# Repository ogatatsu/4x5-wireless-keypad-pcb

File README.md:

# 4x5-wireless-keypad-pcb

## 部品表

| Name | Qty | Description | Manufacturer
----|----|----|----
| U1 | 1 | BL652-SA-01 | LairdTech |
| Y1 | 1 | Crystal, FC-135, 32.768kHz, 9pF | EPSON |
| C1,C2 | 2 | Capacitor, 12pF, 1608 ||
| C3,C4 | 2 | Capacitor, 0.1uF, 1608 ||
| R1 | 1 | Resistor, 1k Ohm, 1608 ||
| R2 | 1 | Resistor, 330 Ohm, 1608 ||
| R3 | 1 | Resistor, 10k Ohm, 1608 ||
| D1~21 | 21 | Diode, 1N4148W | Diodes Incorporated |
| LED1 | 1 | Led, Red, 1608 ||
| LED2 | 1 | Led, Yellow Green, 1608 ||
| SW1~20 | 20 | Switch, Cherry Mx | Cherry |
| BT1,2 | 4 | Battery Clips, BC-0402 | COMFORTABLE ELECTRONIC |

## License

https://creativecommons.org/licenses/by/4.0/

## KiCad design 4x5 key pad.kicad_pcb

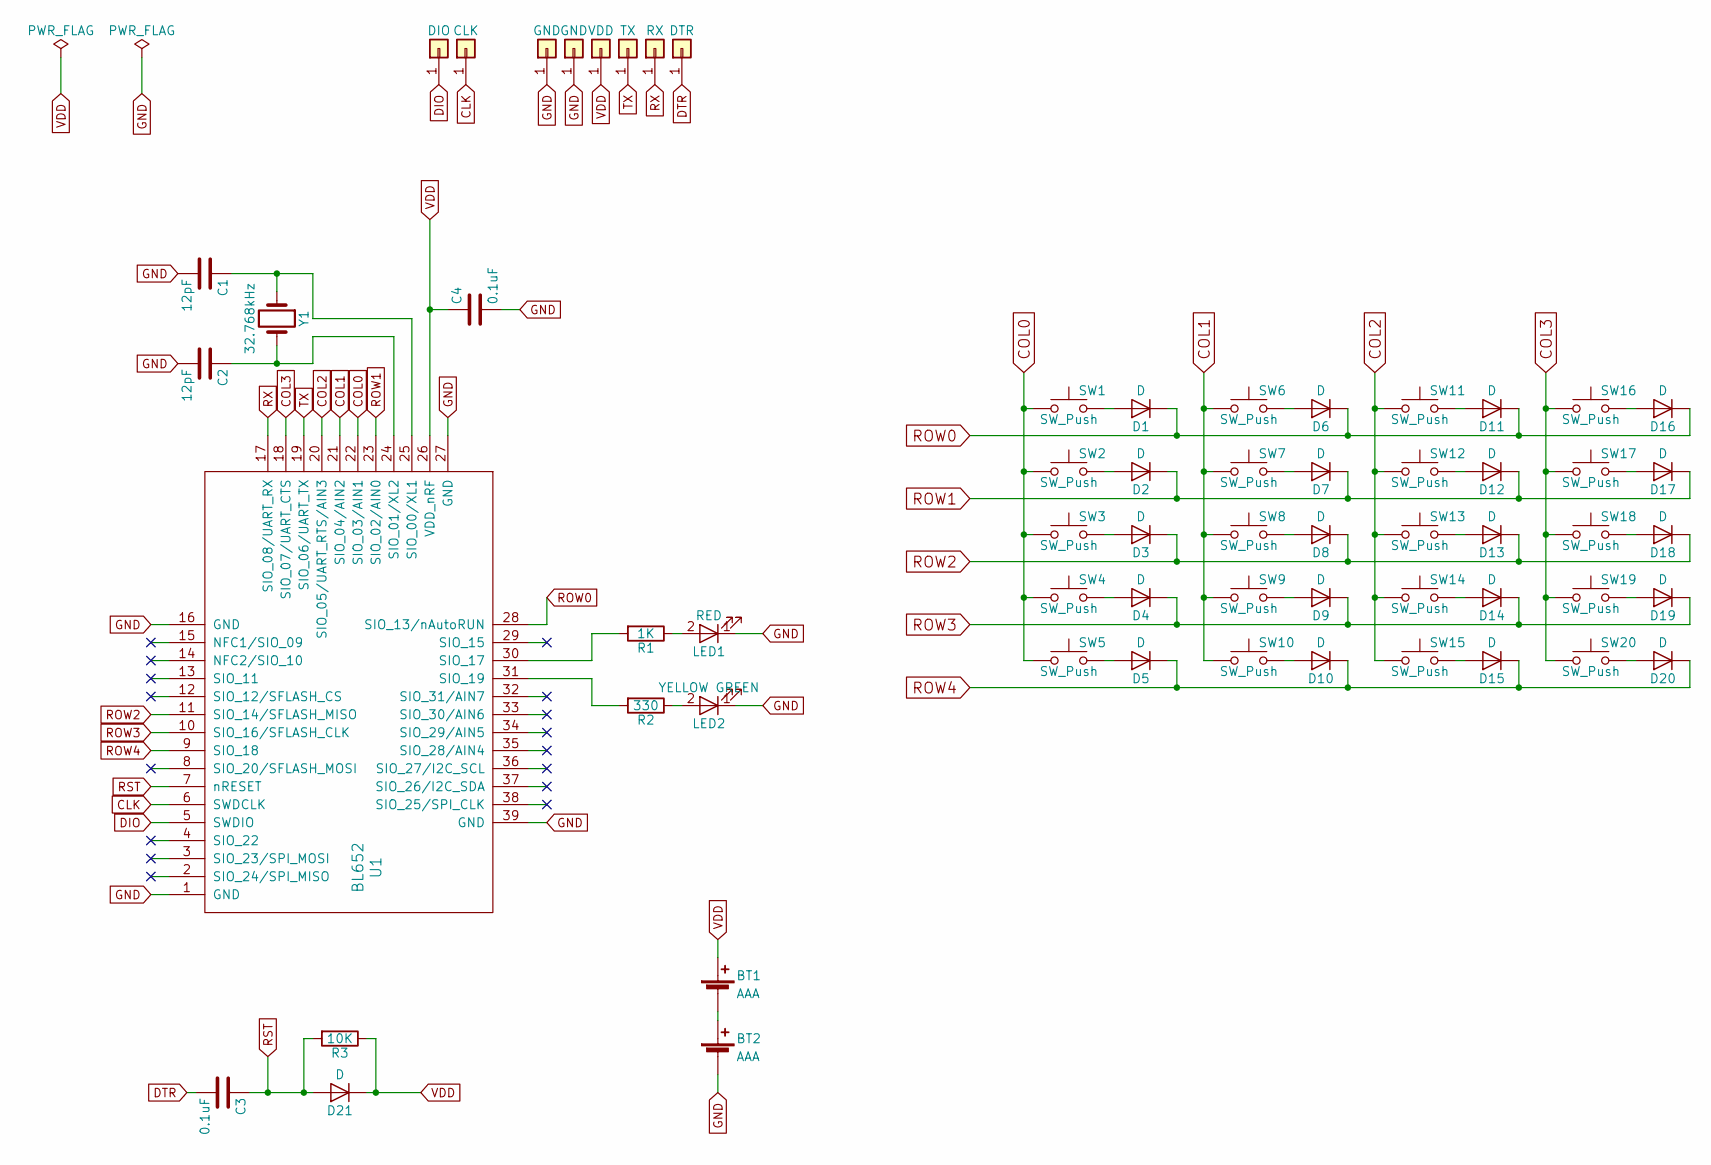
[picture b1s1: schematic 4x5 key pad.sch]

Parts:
BT1, BT2: AAA; AAABatteryClip
C1, C2: 12pF; 1608
C3, C4: 0.1uF; 1608
D1, D2, D3, D4, D5, D6, D7, D8, D9, D10, D11, D12, D13, D14, D15, D16, D17, D18, D19, D20, D21: D; Diode
LED1: RED; 1608
LED2: YELLOW GREEN; 1608
PCLK1: CLK; Wirepad
PDIO1: DIO; Wirepad
PDTR1: DTR; Wirepad
PGND1, PGND2: GND; Wirepad
PRX1: RX; Wirepad
PTX1: TX; Wirepad
PVDD1: VDD; Wirepad
R1: 1K; 1608
R2: 330; 1608
R3: 10K; 1608
SW1, SW2, SW3, SW4, SW5, SW6, SW7, SW8, SW9, SW10, SW11, SW12, SW13, SW14, SW15, SW16, SW17, SW18, SW19, SW20: SW_Push; CherryMx
U1: BL652
Y1: 32.768kHz; FC-135

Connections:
CLK: PCLK1.1, U1.6 (SWDCLK)
COL0: SW1.1, SW2.1, SW3.1, SW4.1, SW5.1, U1.22 (SIO_03/AIN1)
COL1: SW6.1, SW7.1, SW8.1, SW9.1, SW10.1, U1.21 (SIO_04/AIN2)
COL2: SW11.1, SW12.1, SW13.1, SW14.1, SW15.1, U1.20 (SIO_05/UART_RTS/AIN3)
COL3: SW16.1, SW17.1, SW18.1, SW19.1, SW20.1, U1.18 (SIO_07/UART_CTS)
DIO: PDIO1.1, U1.5 (SWDIO)
DTR: C3.2, PDTR1.1
GND: BT2.2 (-), C1.2, C2.2, C4.2, LED1.1 (K), LED2.1 (K), PGND1.1, PGND2.1, U1.1 (GND), U1.16 (GND), U1.27 (GND), U1.39 (GND)
unnamed: BT1.2 (-), BT2.1 (+)
unnamed: C1.1, U1.25 (SIO_00/XL1), Y1.1
unnamed: C2.1, U1.24 (SIO_01/XL2), Y1.2
unnamed: D1.2 (A), SW1.2
unnamed: D2.2 (A), SW2.2
unnamed: D3.2 (A), SW3.2
unnamed: D4.2 (A), SW4.2
unnamed: D5.2 (A), SW5.2
unnamed: D6.2 (A), SW6.2
unnamed: D7.2 (A), SW7.2
unnamed: D8.2 (A), SW8.2
unnamed: D9.2 (A), SW9.2
unnamed: D10.2 (A), SW10.2
unnamed: D11.2 (A), SW11.2
unnamed: D12.2 (A), SW12.2
unnamed: D13.2 (A), SW13.2
unnamed: D14.2 (A), SW14.2
unnamed: D15.2 (A), SW15.2
unnamed: D16.2 (A), SW16.2
unnamed: D17.2 (A), SW17.2
unnamed: D18.2 (A), SW18.2
unnamed: D19.2 (A), SW19.2
unnamed: D20.2 (A), SW20.2
unnamed: LED1.2 (A), R1.1
unnamed: LED2.2 (A), R2.1
unnamed: R1.2, U1.30 (SIO_17)
unnamed: R2.2, U1.31 (SIO_19)
ROW0: D1.1 (K), D6.1 (K), D11.1 (K), D16.1 (K), U1.28 (SIO_13/nAutoRUN)
ROW1: D2.1 (K), D7.1 (K), D12.1 (K), D17.1 (K), U1.23 (SIO_02/AIN0)
ROW2: D3.1 (K), D8.1 (K), D13.1 (K), D18.1 (K), U1.11 (SIO_14/SFLASH_MISO)
ROW3: D4.1 (K), D9.1 (K), D14.1 (K), D19.1 (K), U1.10 (SIO_16/SFLASH_CLK)
ROW4: D5.1 (K), D10.1 (K), D15.1 (K), D20.1 (K), U1.9 (SIO_18)
RST: C3.1, D21.2 (A), R3.2, U1.7 (nRESET)
RX: PRX1.1, U1.17 (SIO_08/UART_RX)
TX: PTX1.1, U1.19 (SIO_06/UART_TX)
VDD: BT1.1 (+), C4.1, D21.1 (K), PVDD1.1, R3.1, U1.26 (VDD_nRF)

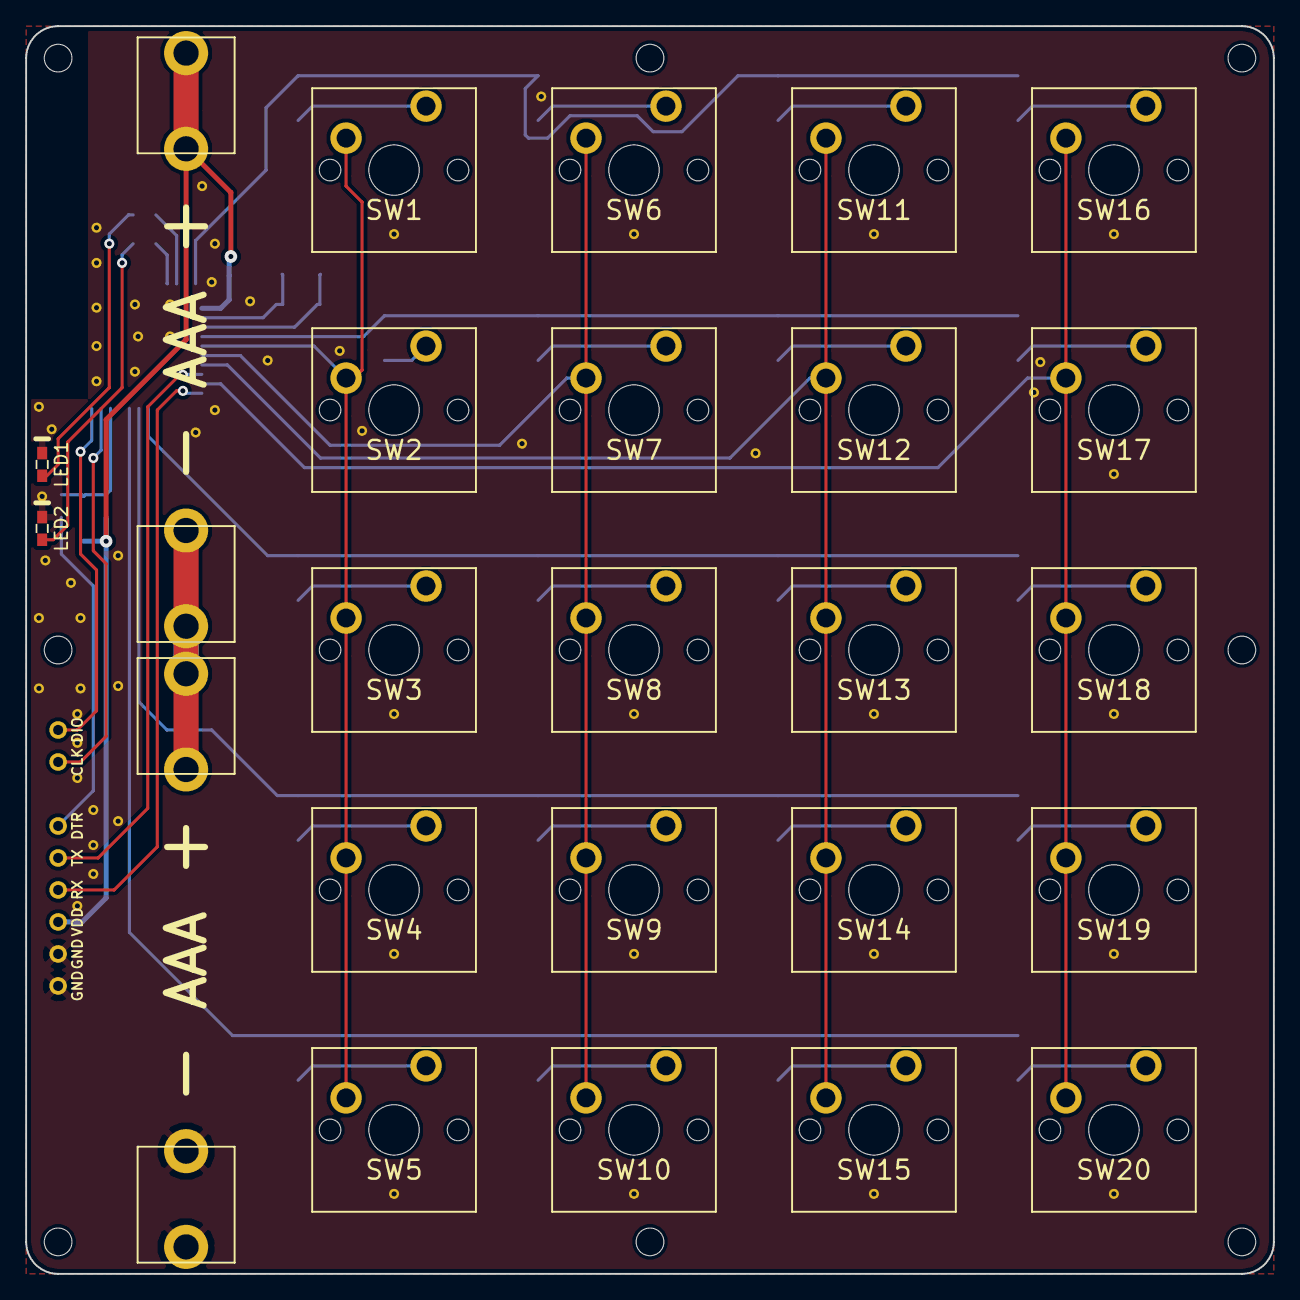
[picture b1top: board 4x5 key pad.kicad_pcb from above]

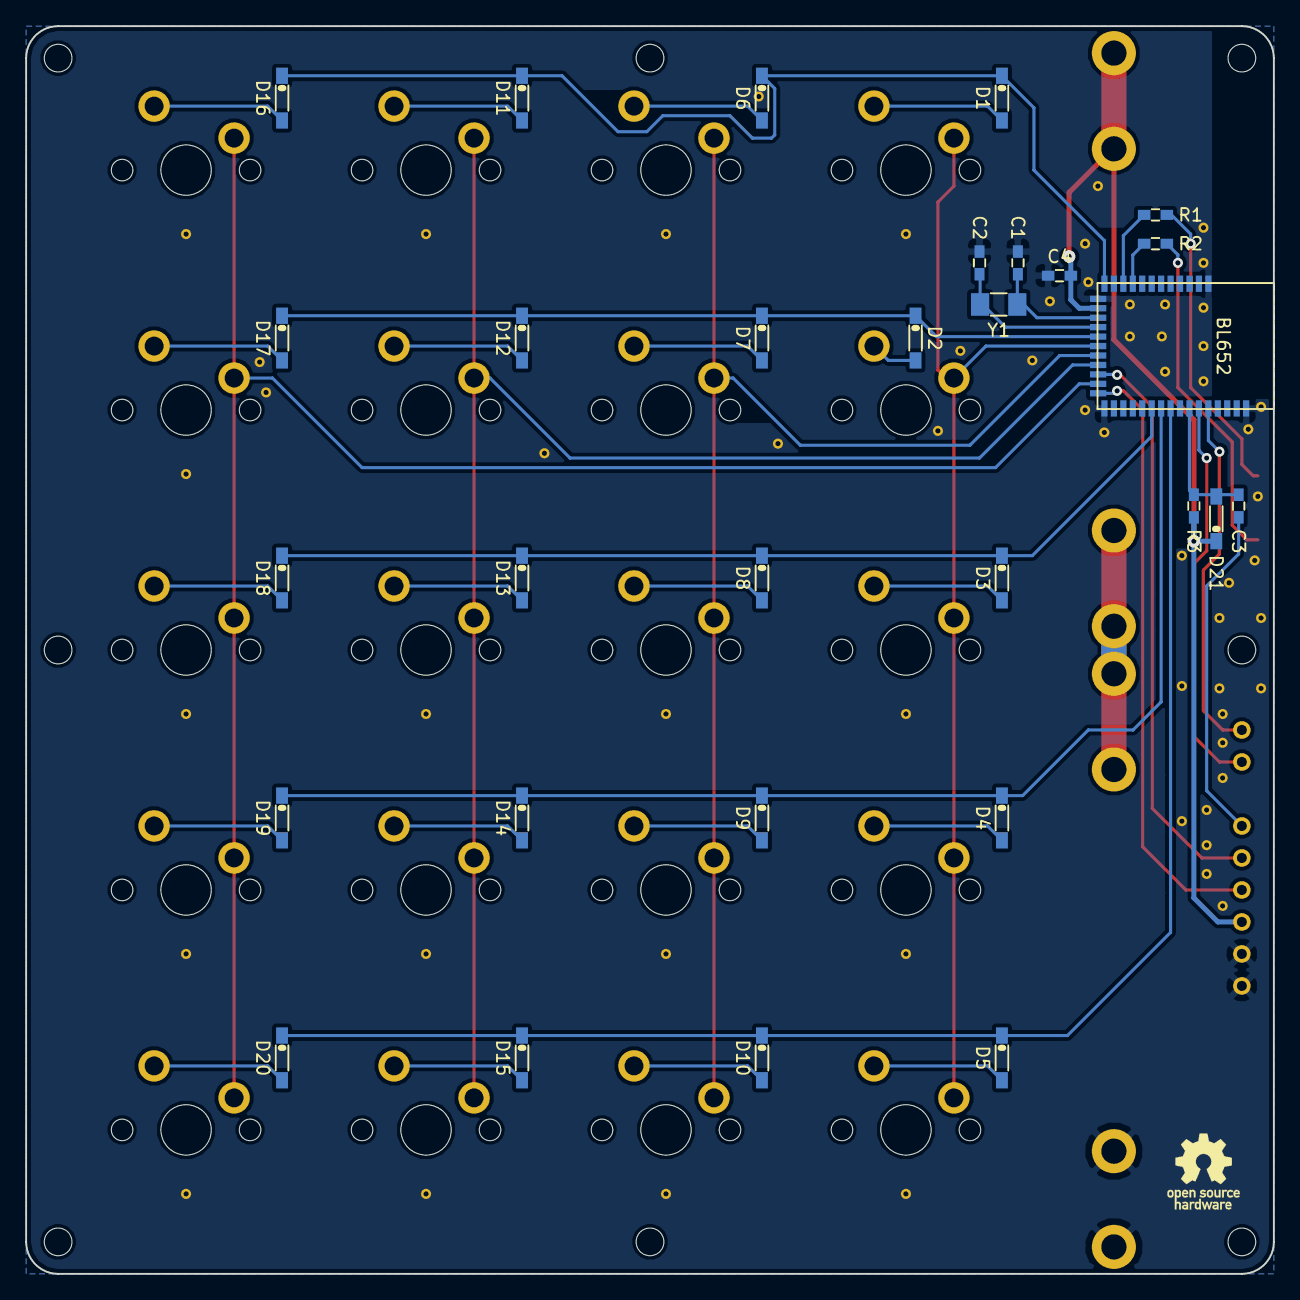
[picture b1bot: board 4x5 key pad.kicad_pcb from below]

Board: 2 copper layers, 99.1 x 99.1 mm, 70 parts (30 on the bottom side), 44 nets.

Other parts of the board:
Hole1, Hole2, Hole3, Hole4, Hole5, Hole6, Hole7, Hole8: MountingHole_2.2mm_M2

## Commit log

2018-01-15 add schematic
2018-01-15 add images
